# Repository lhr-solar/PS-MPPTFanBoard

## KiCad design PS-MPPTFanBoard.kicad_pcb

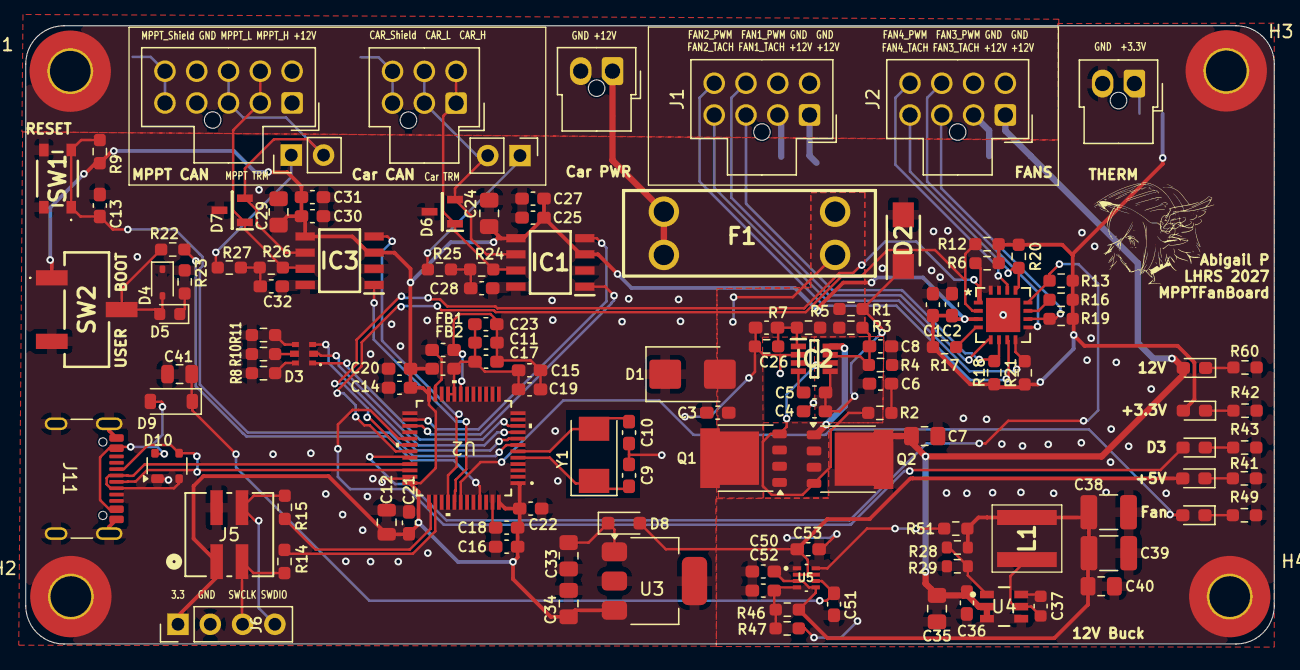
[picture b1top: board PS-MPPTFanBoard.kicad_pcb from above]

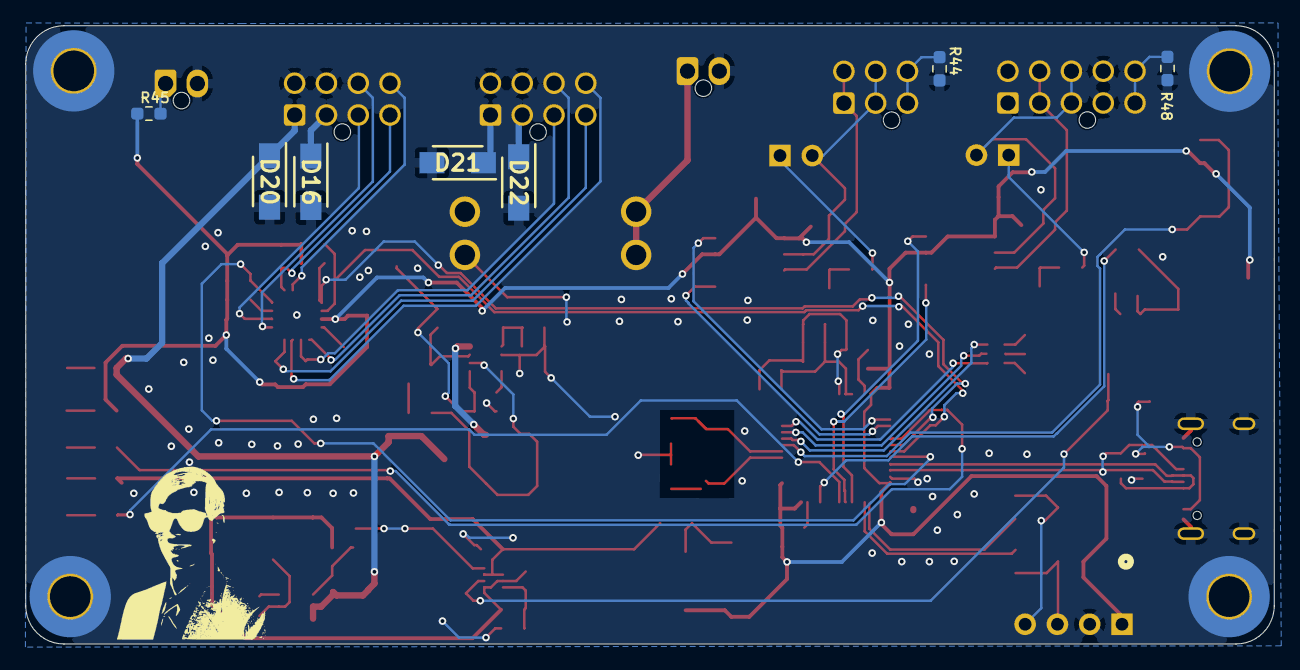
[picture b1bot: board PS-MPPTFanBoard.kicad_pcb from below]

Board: 2 copper layers, 98.2 x 48.6 mm, 138 parts (8 on the bottom side), 77 nets.

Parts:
12V: 12V; LED_0603_1608Metric_Pad1.05x0.95mm_HandSolder
+3.3V: 3.3V; LED_0603_1608Metric_Pad1.05x0.95mm_HandSolder
+5V: 5V; LED_0603_1608Metric_Pad1.05x0.95mm_HandSolder
C1, C2, C17, C19: 1uF; C_0603_1608Metric_Pad1.08x0.95mm_HandSolder
C3, C8, C25, C26, C27, C28, C30, C31, C32, C50, C51, C52, C53: 0.1u; C_0603_1608Metric_Pad1.08x0.95mm_HandSolder
C4: 1u; C_0603_1608Metric_Pad1.08x0.95mm_HandSolder
C5: 220n; C_0603_1608Metric_Pad1.08x0.95mm_HandSolder
C6: 10n; C_0603_1608Metric_Pad1.08x0.95mm_HandSolder
C7, C24, C29, C33, C34: 10u; C_0805_2012Metric_Pad1.18x1.45mm_HandSolder
C9, C10: 26p; C_0603_1608Metric_Pad1.08x0.95mm_HandSolder
C11, C13, C14, C15, C16, C18, C20, C21, C22: 0.1uF; C_0603_1608Metric_Pad1.08x0.95mm_HandSolder
C12: 10uF; C_0805_2012Metric
C23: 100nF; C_0603_1608Metric_Pad1.08x0.95mm_HandSolder
C35: 4.7u; C_0805_2012Metric_Pad1.18x1.45mm_HandSolder
C36: 100n; C_0603_1608Metric_Pad1.08x0.95mm_HandSolder
C37: 100n; C_0603_1608Metric
C38, C39: 22u; C_1210_3225Metric_Pad1.33x2.70mm_HandSolder
C40: 3.3u; C_0805_2012Metric_Pad1.18x1.45mm_HandSolder
C41: 10u; C_0805_2012Metric
Car CAN: Car_CAN; Molex_Nano-Fit_105310-xx06_2x03_P2.50mm_Vertical
Car PWR: Car_Power; Molex_Nano-Fit_105309-xx02_1x02_P2.50mm_Vertical
Car TRM: TRM; PinHeader_1x02_P2.54mm_Vertical
D1: SMBJ15CA; D_SMB
D2: SMAF4758A; SODFL5026X125N
D3: RGB_LED
D3#2: Debug3; LED_0603_1608Metric_Pad1.05x0.95mm_HandSolder
D4: TVS; D_SOD-323
D5: LED; LED_0603_1608Metric
D6, D7: CDSOT23-T24CAN
D8: SBA130CH-AU_R1_000A1; D_SOD-323_HandSoldering
D9: D_Schottky; D_SOD-123
D10: SP0503BAHT; SOT-143
D16, D20, D21, D22: VSSAF522-M3/H; SODFL5026X125N
F1: Fuse_3557_2; Fuse-3557-2
FB1, FB2: FerriteBead; C_0603_1608Metric_Pad1.08x0.95mm_HandSolder
Fan: FanChipStatus; LED_0603_1608Metric_Pad1.05x0.95mm_HandSolder
H1, H2, H3, H4: MountingHole; MountingHole_3.2mm_M3_Pad_TopBottom
IC1, IC3: TCAN3413DR
IC2: LM74502DDFR
J1: Fan 1, 2; Molex_Nano-Fit_105310-xx08_2x04_P2.50mm_Vertical
J2: Fan 3, 4; Molex_Nano-Fit_105310-xx08_2x04_P2.50mm_Vertical
J5: SWD_Header; SWD_Conn
J6: SWD; PinHeader_1x04_P2.54mm_Vertical
J11: USB_C_Receptacle_USB2.0_16P; USB_C_Receptacle_GCT_USB4105-xx-A_16P_TopMnt_Horizontal
L1: 8.2u; XAL5050822MEC
LOGO3: Dr. Hallock; Hallock_Image_Tiny
LOGO4: LHRS; LHRs_LOGO
MPPT CAN: MPPT_CAN; Molex_Nano-Fit_105310-xx10_2x05_P2.50mm_Vertical
MPPT TRM: TRM; PinHeader_1x02_P2.54mm_Vertical
Q1, Q2: PSMN012-100YS; LFPAK56
R1, R6, R9, R12, R13, R22, R45, R46, R51: 10k; R_0603_1608Metric_Pad0.98x0.95mm_HandSolder
R2: 33; R_0603_1608Metric_Pad0.98x0.95mm_HandSolder
R3, R5: 100k; R_0603_1608Metric_Pad0.98x0.95mm_HandSolder
R4: 7.32k; R_0603_1608Metric_Pad0.98x0.95mm_HandSolder
R7: 15.8k; R_0603_1608Metric_Pad0.98x0.95mm_HandSolder
R8, R10, R11, R23, R41, R42, R43, R49: 1k; R_0603_1608Metric_Pad0.98x0.95mm_HandSolder
R14, R15: 22; R_0603_1608Metric_Pad0.98x0.95mm_HandSolder
R16, R17: 33k; R_0603_1608Metric_Pad0.98x0.95mm_HandSolder
R18, R19, R20, R21: 5k; R_0603_1608Metric_Pad0.98x0.95mm_HandSolder
R24, R25, R26, R27: 60; R_0603_1608Metric_Pad0.98x0.95mm_HandSolder
R28: 100k; R_0603_1608Metric
R29: 19.1k; R_0603_1608Metric
R44, R48: 0; R_0603_1608Metric_Pad0.98x0.95mm_HandSolder
R47, R60: 4.7k; R_0603_1608Metric_Pad0.98x0.95mm_HandSolder
SW1: Reset; TL3365AF180QG
SW2: SW_SPDT; BootSW
THERM: Thermistor_Connecter; Molex_Nano-Fit_105309-xx02_1x02_P2.50mm_Vertical
U1: EMC2305-1-AP-TR; QFN16_4x4MC_MCH
U2: STM32G473CETx; 48PinMCU
U3: MCP1826S; SOT-223-3_TabPin2
U4: LMR51635XDDCR; DDC0006A-MFG
U5: TPS2117DRLR
Y1: Crystal; Crystal_SMD_Abracon_ABM3-2Pin_5.0x3.2mm

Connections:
+3.3V: +3.3V.2 (A), C1.1, C2.1, C12.1, C14.1, C16.1, C18.1, C20.1, C21.1, C22.1, C24.1, C25.1, C27.1, C29.1, C30.1, C31.1, C34.2, FB2.1, IC1.3 (VCC), IC1.5 (SHDNV_IO), IC3.3 (VCC), IC3.5 (SHDNV_IO), J5.1, J6.1, R6.2, R9.2, R12.2, R13.2, R16.2, R17.2, R18.2, R19.2, R20.2, R21.2, R45.1, SW2.1 (A), U1.3 (VDD), U2.1 (VBAT), U2.24 (VDD), U2.36 (VDD), U2.48 (VDD), U3.3 (VO)
+5V: +5V.2 (A), C53.1, D8.2 (A), U5.2 (VOUT), U5.7 (VOUT__1)
+12V: 12V.2 (A), C7.1, C35.1, C36.1, D16.1 (K), D20.1 (K), D21.1 (K), D22.1 (K), J1.1, J1.2, J2.1, J2.2, MPPT CAN.1 (12V), MPPT CAN.10 (12V), Q2.5, U4.2 (EN), U4.3 (VIN)
/5V_Buck: C38.1, C39.1, C40.1, C50.1, L1.2, R28.1, R46.1, R51.1, U5.3 (VIN1), U5.5 (MODE)
/12VBuck/CB: C37.1, U4.6 (CB)
/12VBuck/FB: R28.2, R29.1, U4.1 (FB)
/12VBuck/SW: C37.2, L1.1, U4.5 (SW)
/12V_In: C3.1, D1.2 (A2), F1.2, Q1.5, R1.2, R3.1, R5.1
/48PinMCU/BOOT0: R22.1, U2.45 (PB8-BOOT0)
/48PinMCU/NRST: C13.1, R9.1, SW1.1, U2.7 (PG10-NRST)
/48PinMCU/PA0: D3.5, U2.8 (PA0-GPIO_BLUE)
/48PinMCU/PA1: D3.3, U2.9 (PA1_GPIO_RED)
/48PinMCU/PA2: D3.1, U2.10 (PA2-GPIO_GREEN)
/48PinMCU/SWCLK: R14.1, U2.38 (PA14)
/48PinMCU/SWDIO: R15.1, U2.37 (PA13)
/CAR_CAN_H: Car CAN.1 (CAN_H), Car CAN.6 (CAN_H), D6.1 (CAN_H), IC1.7 (CANH), R24.1
/CAR_CAN_L: Car CAN.2 (CAN_L), Car CAN.5 (CAN_L), Car TRM.2 (B), D6.2 (CAN_L), IC1.6 (CANL)
/CAR_CAN_RX: IC1.4 (RXD), U2.26 (PB12)
/CAR_CAN_TX: IC1.1 (TXD), U2.27 (PB13)
/Car_Shield: Car CAN.3 (SHIELD), Car CAN.4 (SHIELD), R44.1
/DEBUG3: D3#2.2 (A), U2.29 (PB15)
/FAN1_PWM: J1.6, U1.5 (PWM1)
/FAN1_TACH: J1.3, R18.1, U1.6 (TACH1)
/FAN2_PWM: J1.5, U1.7 (PWM2)
/FAN2_TACH: J1.4, R21.1, U1.8 (TACH2)
/FAN3_PWM: J2.6, U1.9 (PWM3)
/FAN3_TACH: J2.3, R19.1, U1.10 (TACH3)
/FAN4_PWM: J2.5, U1.14 (TACH4)
/FAN4_TACH: J2.4, R20.1, U1.13 (PWM4)
/FAN_CHIP: Fan.2 (A), U2.42 (PB5)
/FAN_SCL: R12.1, U1.2 (SMCLK), U2.31 (PA9)
/FAN_SDA: R6.1, U1.1 (SMDATA), U2.30 (PA8)
/Fans/ADDR_SEL: R17.1, U1.4 (ADDR_SEL)
/Fans/CLK: R16.1, U1.11 (CLK)
/MPPT_CAN_H: D7.1 (CAN_H), IC3.7 (CANH), MPPT CAN.2 (CAN_H), MPPT CAN.9 (CAN_H), R26.1
/MPPT_CAN_L: D7.2 (CAN_L), IC3.6 (CANL), MPPT CAN.3 (CAN_L), MPPT CAN.8 (CAN_L), MPPT TRM.2 (B)
/MPPT_CAN_RX: IC3.4 (RXD), U2.40 (PB3)
/MPPT_CAN_TX: IC3.1 (TXD), U2.41 (PB4)
/MPPT_Shield: MPPT CAN.5 (SHIELD), MPPT CAN.6 (SHIELD), R48.1
/PowerProtection/EN/UVLO: C26.1, IC2.1 (EN/UVLO), R5.2, R7.2
/PowerProtection/OV: C8.1, IC2.7 (OV), R3.2, R4.1
/PowerProtection/gate: IC2.6 (GATE), Q1.4, Q2.4, R2.2
/PowerProtection/source: IC2.8 (SRC), Q1.1, Q1.2, Q1.3, Q2.1, Q2.2, Q2.3
/Power_Mux/PR1: C52.1, R46.2, R47.1, U5.4 (PR1)
/USB-C_Connector/VBUS_IN: D9.2 (A), D10.4 (K), J11.A4 (VBUS), J11.A9 (VBUS), J11.B4 (VBUS), J11.B9 (VBUS)
/USB_5V: C41.2, C51.1, D9.1 (K), U5.6 (VIN2)
/USB_D+: D10.2 (K), J11.A6 (D+), J11.B6 (D+), U2.33 (PA11)
/USB_D-: D10.3 (K), J11.A7 (D-), J11.B7 (D-), U2.34 (PA12)
/~SMBALERT: R13.1, U1.12 (*ALERT), U2.32 (PA10)
AGND: C11.2, C15.2, C17.2, C19.2, C23.2, FB1.1, U2.19 (VSSA)
GND: C1.2, C2.2, C3.2, C4.1, C6.2, C7.2, C8.2, C9.1, C10.2, C12.2, C13.2, C14.2, C16.2, C18.2, C20.2, C21.2, C22.2, C24.2, C25.2, C26.2, C27.2, C28.1, C29.2, C30.2, C31.2, C32.1, C33.1, C34.1, C35.2, C36.2, C38.2, C39.2, C40.2, C41.1, C50.2, C51.2, C52.2, C53.2, Car PWR.2 (GND), D1.1 (A1), D2.2 (A), D4.1 (A1), D6.3 (GND), D7.3 (GND), D10.1 (A), D16.2 (A), D20.2 (A), D21.2 (A), D22.2 (A), FB1.2, IC1.2 (GND), IC1.8 (STB), IC2.2 (GND), IC3.2 (GND), IC3.8 (STB), J1.7, J1.8, J2.7, J2.8, J5.2, J6.2, J11.A1 (GND), J11.A12 (GND), J11.B1 (GND), J11.B12 (GND), J11.S1 (SHIELD), J11.S2 (Shield), J11.S3 (Shield), J11.S4 (Shield), MPPT CAN.4 (GND), MPPT CAN.7 (GND), R4.2, R7.1, R8.2, R10.2, R11.2, R23.2, R29.2, R41.2, R42.2, R43.2, R44.2, R47.2, R48.2, R49.2, R60.2, SW1.2, SW2.3 (C), THERM.2, U1.HTAB (EPAD), U2.23 (VSS), U2.35 (VSS), U2.47 (VSS), U3.2 (GND), U4.4 (GND), U5.1 (GND)
unnamed: C6.1, R2.1
unnamed: C28.2, R24.2, R25.1
unnamed: C32.2, R26.2, R27.1
unnamed: C4.2, C5.1, D2.1 (K), IC2.5 (VS), R1.1
unnamed: D3.2, R8.1
unnamed: D3.4, R10.1
unnamed: D3.6, R11.1
unnamed: D4.2 (A2), D5.2 (A), R22.2, SW2.2 (B)
unnamed: D5.1 (K), R23.1
unnamed: C33.2, D8.1 (K), U3.1 (VI)
unnamed: Fan.1 (K), R49.1
unnamed: 12V.1 (K), R60.1
unnamed: +5V.1 (K), R41.1
unnamed: +3.3V.1 (K), R42.1
unnamed: D3#2.1 (K), R43.1
unnamed: C5.2, IC2.4 (VCAP)
unnamed: J5.3, J6.3, R14.2
unnamed: J5.4, J6.4, R15.2
unnamed: Car PWR.1 (+12V), F1.1
unnamed: R45.2, THERM.1
unnamed: Car TRM.1 (A), R25.2
unnamed: MPPT TRM.1 (A), R27.2
unnamed: C9.2, U2.5 (PF0-OSC_IN), Y1.1
unnamed: C10.1, U2.6 (PF1-OSC_OUT), Y1.2
unnamed: R51.2, U5.8 (ST)
VDDA: C11.1, C15.1, C17.1, C19.1, C23.1, FB2.2, U2.20 (VREF+), U2.21 (VDDA)

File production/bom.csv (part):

"Reference","Qty","Value","Footprint","Datasheet","P/N","PN","p/n"
"J6","1","SWD","Connector_PinHeader_2.54mm:PinHeader_1x04_P2.54mm_Vertical","","","",""
"JP1,JP2","2","TRM","Connector_PinHeader_2.54mm:PinHeader_1x02_P2.54mm_Vertical","","","",""
"LOGO3","1","Dr. Hallock","LHRS_Logos:Hallock_Image_Tiny","","","",""
"LOGO4","1","LHRS","LHRS_Logos:LHRs_LOGO","","","",""
"J5","1","SWD_Header","LHRS_Connectors:SWD_Conn","kicad-embed://Conn_02x02_Odd_Even.pdf","0878320406","",""
"J9","1","Car_Power","LHRS_Connectors:Molex_Nano-Fit_105309-xx02_1x02_P2.50mm_Vertical","","1053091102","",""
"J8","1","Car_CAN","LHRS_Connectors:Molex_Nano-Fit_105310-xx06_2x03_P2.50mm_Vertical","","1053101106","",""
"J7","1","MPPT_CAN","LHRS_Connectors:Molex_Nano-Fit_105310-xx10_2x05_P2.50mm_Vertical","","1053101110","",""
"SW2","1","SW_SPDT","LHRS_Special:BootSW","kicad-embed://BootSW.pdf","450406020024","",""
"C1,C2,C17,C19","4","1uF","Capacitor_SMD:C_0603_1608Metric_Pad1.08x0.95mm_HandSolder","","C0805C105K5PACTU,MLASU168SB5105KTNA01","",""
"C3,C8,C25,C26,C27,C28,C30,C31,C32,C50,C51,C52,C53","13","0.1u","Capacitor_SMD:C_0603_1608Metric_Pad1.08x0.95mm_HandSolder","","CL10B104KB8NNNC,MLASH168SB7104KTNA01","",""
"C7,C24,C29,C33,C34","5","10u","Capacitor_SMD:C_0805_2012Metric_Pad1.18x1.45mm_HandSolder","","GRM21BR61H106KE43K,GRM21BR61H106KE43L","",""
"R1,R6,R9,R12,R13,R22,R45,R46,R51","9","10k","Resistor_SMD:R_0603_1608Metric_Pad0.98x0.95mm_HandSolder","","CRCW060310K0FKEI ,CRCW06031K00FKEI","",""
"R8,R10,R11,R23,R41,R42,R43,R49","8","1k","Resistor_SMD:R_0603_1608Metric_Pad0.98x0.95mm_HandSolder","","CRCW06031K00FKEI,CRCW06031K00FKEI ","",""
"C9,C10","2","26p","Capacitor_SMD:C_0603_1608Metric_Pad1.08x0.95mm_HandSolder","","0603N270F500CT ","",""
"R16,R17","2","33k","Resistor_SMD:R_0603_1608Metric_Pad0.98x0.95mm_HandSolder","","0603WAF3302TDE","",""
"R3,R5","2","100k","Resistor_SMD:R_0603_1608Metric_Pad0.98x0.95mm_HandSolder","","0603WAF1003T5E","",""
"C35","1","4.7u","Capacitor_SMD:C_0805_2012Metric_Pad1.18x1.45mm_HandSolder","","08055D475KAT4A","",""
"J10","1","Thermistor_Connecter","LHRS_Connectors:Molex_Nano-Fit_105309-xx02_1x02_P2.50mm_Vertical","","105309-1102","",""
"J1","1","Fan 1, 2","LHRS_Connectors:Molex_Nano-Fit_105310-xx08_2x04_P2.50mm_Vertical","","105310-1108","",""
"J2","1","Fan 3, 4","LHRS_Connectors:Molex_Nano-Fit_105310-xx08_2x04_P2.50mm_Vertical","","105310-1108","",""
"D3","1","RGB_LED","LHRS_Special:RGB_LED","kicad-embed://EVER-S-A0007433884-1.pdf","19-337/R6GHBHC-A01/2T ","",""
"F1","1","Fuse_3557_2","LHRS_Power:Fuse-3557-2","kicad-embed://3557-2-datasheet.pdf","3557-2","",""
"Y1","1","Crystal","LHRS_Passives:Crystal_SMD_Abracon_ABM3-2Pin_5.0x3.2mm","kicad-embed://HSE_Crystal.pdf","ABM3-8.000MHZ-D2Y-T","",""
"D9","1","D_Schottky","Diode_SMD:D_SOD-123","","BAT760-7","",""
"FB1,FB2","2","FerriteBead","Capacitor_SMD:C_0603_1608Metric_Pad1.08x0.95mm_HandSolder","kicad-embed://FerriteBead.pdf","BLM18PG121SH1D","",""
"C40","1","3.3u","Capacitor_SMD:C_0805_2012Metric_Pad1.18x1.45mm_HandSolder","","C2012X5R1H335K125AB","",""
"C6","1","10n","Capacitor_SMD:C_0603_1608Metric_Pad1.08x0.95mm_HandSolder","","CC0603KRX7R9BB103","",""
"C4","1","1u","Capacitor_SMD:C_0603_1608Metric_Pad1.08x0.95mm_HandSolder","","CC0603KRX7R9BB105","",""
"C5","1","220n","Capacitor_SMD:C_0603_1608Metric_Pad1.08x0.95mm_HandSolder","","CC0603KRX7R9BB224","",""
"D6,D7","2","CDSOT23-T24CAN","LHRS_Passives:CDSOT23-T24CAN","kicad-embed://cdsot23-t24can.pdf","CDSOT23-T24CAN","",""
"R44,R48","2","0","Resistor_SMD:R_0603_1608Metric_Pad0.98x0.95mm_HandSolder","","CRCW06031K00FKEI","",""
"R47,R60","2","4.7k","Resistor_SMD:R_0603_1608Metric_Pad0.98x0.95mm_HandSolder","","CRCW06031K00FKEI","",""
"R18,R19,R20,R21","4","5k","Resistor_SMD:R_0603_1608Metric_Pad0.98x0.95mm_HandSolder","","CRCW06035K10FKEC","",""
"R7","1","15.8k","Resistor_SMD:R_0603_1608Metric_Pad0.98x0.95mm_HandSolder","","CRCW060315K8FKEA","",""
"R29","1","19.1k","Resistor_SMD:R_0603_1608Metric","","CRCW060319K1FKEAHP","",""
"R24,R25,R26,R27","4","60","Resistor_SMD:R_0603_1608Metric_Pad0.98x0.95mm_HandSolder","","CRCW060360R4FKEA","",""
"R28","1","100k","Resistor_SMD:R_0603_1608Metric","","CRCW0603100KFKEE","",""
"U1","1","EMC2305-1-AP-TR","fanboard:QFN16_4x4MC_MCH","https://ww1.microchip.com/downloads/aemDocuments/documents/M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","EMC2305-1-AP-TR","",""
"R14,R15","2","22","Resistor_SMD:R_0603_1608Metric_Pad0.98x0.95mm_HandSolder","","FRC0603F22R0TS","",""
"C38,C39","2","22u","Capacitor_SMD:C_1210_3225Metric_Pad1.33x2.70mm_HandSolder","","GMK325BJ226MM-P","",""
"C12","1","10uF","Capacitor_SMD:C_0805_2012Metric","","GRM21BR61H106KE43K","",""
"IC2","1","LM74502DDFR","LHRS_Power:LM74502DDFR","kicad-embed://LM74502DDFR.pdf","LM74502DDFR","",""
"U4","1","LMR51635XDDCR","LHRS_ICs:DDC0006A-MFG","kicad-embed://lmr51635.pdf","LMR51635XDDCR","",""
"D5","1","LED","LED_SMD:LED_0603_1608Metric","kicad-embed://Blue LED.pdf","LTST-C193TBKT-5A","",""
"U3","1","MCP1826S","Package_TO_SOT_SMD:SOT-223-3_TabPin2","http://ww1.microchip.com/downloads/en/DeviceDoc/22057B.pdf","MCP1826S-3302E/DB","",""
"R2","1","33","Resistor_SMD:R_0603_1608Metric_Pad0.98x0.95mm_HandSolder","","MCT06030C3309FP500","",""
"C11,C13,C14,C15,C16,C18,C20,C21,C22","9","0.1uF","Capacitor_SMD:C_0603_1608Metric_Pad1.08x0.95mm_HandSolder","","MLASH168SB7104KTNA01","",""
"C23","1","100nF","Capacitor_SMD:C_0603_1608Metric_Pad1.08x0.95mm_HandSolder","","MLASH168SB7104KTNA01","",""
"C36","1","100n","Capacitor_SMD:C_0603_1608Metric_Pad1.08x0.95mm_HandSolder","","MLASH168SB7104KTNA01","",""
"C37","1","100n","Capacitor_SMD:C_0603_1608Metric","","MLASH168SB7104KTNA01","",""
"D4","1","TVS","Diode_SMD:D_SOD-323","kicad-embed://TVS.pdf","PESD15VL1BA","",""
"Q1,Q2","2","PSMN012-100YS","Package_TO_SOT_SMD:LFPAK56","kicad-embed://PSMN012-100YS.pdf","PSMN012-100YSFX","",""
"R4","1","7.32k","Resistor_SMD:R_0603_1608Metric_Pad0.98x0.95mm_HandSolder","","RT0603BRE077K32L","",""
"D8","1","SBA130CH-AU_R1_000A1","Diode_SMD:D_SOD-323_HandSoldering","https://www.mouser.com/datasheet/3/3736/1/11145663EF9055F8C1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","SBA130CH-AU_R1_000A1 ","",""
"D2","1","SMAF4758A","LHRS_Passives:SODFL5026X125N","kicad-embed://SMAF4758A.pdf","SMAF4758A","",""
"D1","1","SMBJ15CA","Diode_SMD:D_SMB","kicad-embed://SMBJ15CA.pdf","SMBJ15CA","",""
"D10","1","SP0503BAHT","Package_TO_SOT_SMD:SOT-143","kicad-embed://Littelfuse-TVS-Diode-Array-SP05-Datasheet.pdf","SP0503BAHTG","",""
"U2","1","STM32G473CETx","LHRS_Special:48PinMCU","kicad-embed://stm32g473cb.pdf","STM32G473CET6","",""
"IC1,IC3","2","TCAN3413DR","LHRS_Passives:TCAN3413DR","kicad-embed://tcan3413.pdf","TCAN3413DR","",""
"SW1","1","Reset","LHRS_Special:TL3365AF180QG","kicad-embed://ResetBtn.pdf","TL3365AF180QG","",""
"C41","1","10u","Capacitor_SMD:C_0805_2012Metric","","TMK212BBJ106MGHT","",""
"U5","1","TPS2117DRLR","LHRS_Power:TPS2117DRLR","kicad-embed://tps2117-datasheet.pdf","TPS2117DRLR","",""
"J11","1","USB_C_Receptacle_USB2.0_16P","LHRS_Connectors:USB_C_Receptacle_GCT_USB4105-xx-A_16P_TopMnt_Horizontal","https://www.usb.org/sites/default/files/documents/usb_type-c.zip","USB4105-GF-A","",""
"D16,D20,D21,D22","4","VSSAF522-M3/H","LHRS_Passives:SODFL5026X125N","https://www.wolfspeed.com/media/downloads/103/C3D25170H.pdf","VSSAF522-M3/H","",""
"L1","1","8.2u","LHRS_Power:XAL5050822MEC","","XAL5050-822MEC","",""
"D18","1","FanChipStatus","LED_SMD:LED_0603_1608Metric_Pad1.05x0.95mm_HandSolder","https://mm.digikey.com/Volume0/opasdata/d220001/medias/docus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","XL-1608UBC-06A","",""
"D19","1","12V","LED_SMD:LED_0603_1608Metric_Pad1.05x0.95mm_HandSolder","https://mm.digikey.com/Volume0/opasdata/d220001/medias/docus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","XL-1608UBC-06A","",""
"D23","1","5V","LED_SMD:LED_0603_1608Metric_Pad1.05x0.95mm_HandSolder","https://mm.digikey.com/Volume0/opasdata/d220001/medias/docus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","XL-1608UBC-06A","",""
"D24","1","3.3V","LED_SMD:LED_0603_1608Metric_Pad1.05x0.95mm_HandSolder","https://mm.digikey.com/Volume0/opasdata/d220001/medias/docus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","XL-1608UBC-06A","",""
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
